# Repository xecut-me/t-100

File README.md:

# Siemens Teleprinter 100

Это [телетайп](https://ru.wikipedia.org/wiki/%D0%A2%D0%B5%D0%BB%D0%B5%D1%82%D0%B0%D0%B9%D0%BF) 1963 года, который мы купили и поставили в хакспейсе. Кстати tty в линуксе берется именно отсюда.

Суть телетайпа в том, что это как печатная машинка, но подключенная по телеграфной линии. То, что печатается на клавиатуре, уходит по проводам, а то что приходит печатается на бумаге

Maximum line length = 68 symbols

# AI печатная машинка

## Установка

```bash
cd server
pip install -r requirements.txt
curl -fsSL https://deno.land/install.sh | sh
```

## Запуск

Задать переменные окружения:
- `LLAMA_API_URL` - URL LLM API (например `https://localhost:8080/v1/chat/completions`)
- `LLAMA_API_KEY` - ключ API

Запуск через сокет (подключение к телетайпу по сети):

```bash
deno run --allow-all socket_runner.ts
```

## Как работает

- `server/llm_core.py` - основная логика общения с LLM, стриминг ответов посимвольно
- `server/socket_runner.ts` - Deno скрипт для подключения к телетайпу по TCP сокету (192.168.10.124:1337)

Телетайп притворяется машиной из 1970-х (дата минус 50 лет), отвечает только символами кода Бодо ITA2.

Команда `CLR` или `CLEAR` очищает историю диалога.

# Loopback

Подключается токовая петля и тогда то что уходит, то и приходит. TODO: картинки

### Схема

<table width="100%">
  <tr>
    <td></td>
    <td></td>
  </tr>
  <tr>
    <td></td>
    <td></td>
  </tr>
</table>

## Используемый код

Используется [код Бодо ITA2](https://ru.wikipedia.org/wiki/%D0%9A%D0%BE%D0%B4_%D0%91%D0%BE%D0%B4%D0%BE#ITA2)

# Схемотехника

[Схема в circuit.js](https://www.falstad.com/circuit/circuitjs.html?ctz=CQAgjAzCAMB00IQVhBJsBs0BMAWDWGA7NEUQJxghLTXW1ICmAtGGAFABKMI5GIzDLl79atXLTw8xsJOwBOIPLWLZUEfqp4boCkZKT8+tMOTUnyuxUjBrKam3aKjwADl0BzfSFdgjWH1xXaXYAdxAhSQkI6OxDGHYAExiDTVjXYLVExgAzAEMAVwAbABdmIsZE9lwwWghoYTNgiVpXPnAcFAA-ABUAGVwIKmgAHQBnaIxxsBZbcbgiCDQMbEgkclcyWyR5+Yjx7FnsceY4V1xV3DNyG4bN6AhdsbFpk7OLsCvsG8sgkkfnrBFstVmgNls4tMJOMuiUioMZolmABHAB2AH1KjBxhBsO5sWNlC8xkRsAgCUtYEtqTTaZpprBDqxjoDSWwyEMkN91v8nioDrBcEc3vBEBpFoZyIsMmAkEQwK4ds89qMxmARYgHsRllKIDK5QqlQtVmAObLuVKHlDVbD4UNKiiMQ6AIJgRkEhWwBXe3y+n37QmMzXB4MQYWA4iuXFIVzEOVgzZ8gO4QUhtMzZnzeB+KVxGqm4E0QZJ1XqwHQHOkpD5jloBoAuCR6Oxojx9aJtXQsa2hEOtGYpHO7Du1XuYmTabhhYPChIQxYchclZJqaE8OnWCuMmxvj1dy2KVGlWvMYbrfQHcYPcV76trP-Wfz6CL7DLzs2uG9pH9rGqlrj-k1SnIEGlWasICuRco3OFcDnXOBamgLkGk+CRqyIXwSxPDdEOQmpcDQ3AMLLacPnAyCYz1XBrRhT97W-J1klHQCmFYBsgTJUkCEVCAbgItBYKAzNTwWDDKHWGhyCWbB5VcLC1RFMg2llRdn2k2T70418MB4vjBiVT4PztRFHQHZhnTgFBmIDDM5hEkDcT4dxKC3ChqOVZ4AzDYS4E1RVNhoB5sDiXFTAbY9TxI0UEH81sEFxELVikxSgqc58FRk8h3KwWjjL7AAHAcCXxVdbJZDd-hwXMlnuUgSL2VdvLst01LQc4iP4tAY3k1gGVamMCKITq5zk+zKtvbAapIOrxhy7s6JM5FCt-cYx2K8k-0Asr71lJBcT1WwZPlIjBKZOzWE3II-C619VlbUbVWJMsLvOXwrznW7TW61ldv23xgq2E731yr9TJWtUaGKgNWLshYdNqCDLA2Z85Xcx6bNmZ7hzlPhFj8ZD1khDynpObGKG1fGyUJo0gXhh4rmfZzUZo+a8oYsznSs6ZNQJCchPOlroCwAiKwwojbCCU7w2HAKiOcJYyHE6tZnCzzSwFWWyCvCBFd2oU2JOQXhYkU1znlPBRsMkH6LB5IWR7G3EiK0tECUa2TKdrFSsxhlXsgE2NmrPwiCl1hnoQ5AKwgvGhq5WM+T0f3hC0JOIgvbR6jCcAhjUFOIOT0kEnCSBbB8Pxs7xMvRCzyBK7e7OAnr3QddoYxwFLtvTX4KAxCzzuzG8Lui8HjuAnaXRwkcEACOCKeWgSIpvBkuwAlxMQYCpQK01DDfNSEOJfl4jRlEXYe2+Xpf4gn7w15vnSEgAN3AIsQEWfhZQaCJC+EFBIas6RZA13zmnYIH9k7p2vmAkBz9P5aEgToKu4ALjCCbjXZBiCoGoOLi-euUC34JEUK9agA8iEYCvh0XQABjQIwQtBENJOIJQsht4hn1kQJQKYKyQHzrgQwbQtw91FMMLOpD4ikMLroZItQpC32kcIZQShwAADkWi4GqA8JB6c47Pw0MQ8w4ByDoiEOiaA6IJA3HREgEx8A4jolYOibA6JTDoggOoqAtRJjCFsPiUw+jbBGNwCYsxz5DESGsUhOxYAHFOMca4iQ7jID8HnrYIQ09UkqACUE8xoTTG+SFrY+xEBLFBKsUUvoABRAAIlnKeCjIgcN7uEep9Rk7pGCFYFIqAySdI0O0ihWdmndOaZ-a+c9yT1PntfCZ4zoi9ISPE7OA84jv2Ql09ejjjGmOyU43J8ArH2McbEmuOAvEDzkQ04ethy64JzogyBJyDErwsOYdgLd1D8DWksD57Qe7zI0XiYIVFp7lxnjwC4mSinbLCb5bYkSnHqPYbUQuYsKHBBRdIuQxc-DBFwasD55dIHYtfucdu98SDCEJWSz+bB75wJrkSvOpc6U1FbgPBhvAB71KoL0AYQxeZbXgvAEgKxZTkoQBcdwqtAJnXKghK83IZJbiELxWwIdiYehFNdBVGFXyDHsGqjcpB8mioaOKvEVpgas1Bj+JiOJzUEiJASBhxJKS0jddSekapGTAVIINMheohDOHQmq9Gq5hz6zssOFpOslgxnJoqBUPt1Xq0DNGwsmwnI2FcEm3yQ0iL+tjPm4NLMHaLUYuZN05hpiuC9H6Ot-ow1BhYZqJqLJc1+r2ouPiOq0YNXGCmf8zbtqRVFAQZwnwuRkg2BgFg5B5LPSNsQDAE7gqMxncwOd5Y81Bt4usLKPaS0LT7OWocI5VobX7QK4ShqyHejAkEPEFAQ19rXNeuA3xlnnjMMuvUGh50ig-Xwqdr5IBRlXDerNVzqxbgzWqq2VqbY2v5ReiYV7YZCo7bxHSCAryylDudXyt7-qgWAwReqatsKEcg2SC4pGahZl9UWrDY5cMGS7KW49ztz3QxVgx7dBaKyUA6s+zy3sfKMnErKGephgSxlXOjFN77JPViurqAN8mMNMf3EJoacH2NHvZi6Sy60MbidMBsLKgVl0EFvA9F9raTgYCBPLSaWUhBsHFDmiKvVTxOa1vtNz+ZPNhyzOZtovCcN+BWFKUac0OPfmWrasYJVJxmZuOFmgH8soXD1IJBzgIBoXg0FcNgZtl09SioVsDJWFT5qimFyzFZJIEUmrFoy1rEvrWJGtTapmCOMlNA8cLq68XEF7aJuCb6qTnAVDpwwk0-ANH-fZKis3PithWEMYWAHBt6iyiNqLQ1D1s1th6SGo4ePCQgF6T6BAroleCuuuzE3+bhy9MQD+VN3B4D4G2iKb3g6faQt9q4b5rspNG-d+wr4WCW30ydm15kuZqh5r1sT-XV1tADYWqUvD5MvplSca7vFcZIQi2JOWsxHr-aJ1SG4xAyc0Ap2QKnAHtxSVjDj2OpV4fWsYm7BDHsuMo-JPbAzzBPbJHR1FVbykiJ4DxJ2-Db2hbUdAvgMhM4E7FweTpUBpBc4ZEuQbiIRukVqBRboEo3gyFGErrbxRVBmCTU3CpyIsYrN6g3lql8YklikD2u48k2R8jFBKHoJoiDI-4JUNfSP9c25YI5RbrkyfX66Lj2y3R0eM-HPTg785Dv7lSAL7ro3ceAgO6lJoK+fd7eFxz9XcIkf6mR7lE33gld2-eG7x02o8QsCgPNNAuomcdcl-iIXiBxyS-p375oaf3BSvgNAZNXOECwUMGkBvTF7dU+D-biSg-18iGExodQZwfyoB69fqn+uTdqBFM2cEixVjfL7KiY4vaLi+6N3LucpPAA--E3VBBZVsNQUFDIBgUuBgDZQJDAF-VwYJaxKJexDgcIU-S-NvS-TwagUuDxaAtQWocvM+AIbvNuOZXQbgKAnwVockfEdeWIClABXfGg-ERPRpbwdgseauFSPA3OKQKeFTCIJQEwZtJhXfIQgifg6eIIYeKeFYH+JlWvN5KeVCGQ3xVAEISefA6QqeceGpfAgeWpaIKgpQQubvYKH+HAxRP+bfSyLOC+bvUHC-auRQfAYQNACA1JAFHgMka+DwpQI3QIhRAInw6IEwzgwIrwtJYQSZLOQI+eMZTg+hbpehXPDAuQ-BRvM+S-UvfPWvBZc3cwog-w95PwpA5-KFXZCJA5BxJA1xcfTw7pc5SgmfTw++Cg++AI8udofQjvVuJJXojvNQ01GQ6veQjuUuKeHrdga3UFdlKedlIggQT0JYQYKMc1LbCCKyS6KdRAfwuMXhChEAMYfKAAS0oRYBD0KFKEMIt0-gUNr3CC+Q6BkV0QIOHleM+NGNMKzjmTbhqH8CiOGPEGuQ2gSPBMINoKiKyO6VePZWvleK0ARJGS4AuRTk5QkU3zoHXgcJeN0XJXKMRP+N0U+UJO6VGVLjWiWNzwWQvkW2nlFykFaDgJcRfxyXCQ-3hSAA)

# Оригинальная документация

- t100fullmanual.pdf - для человеков
- t100fullmanual.txt - OCR as is, для LLM-ок

# Тематические стикеры

# Фича с отправкой своего адреса

Есть спец код который посылаешь 2 раза и машина печатает свой адрес

Адрес кодируется вот такими пинами

# Прочая информация

1.8W raspberry
4.2W raspberry + arduino

## Форматтеры

- autopep8
- clang format

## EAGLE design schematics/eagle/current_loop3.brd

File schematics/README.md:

# Схема адаптера токовой петли

## Отступления схемы от реального железа

1. Q2 установлен BD139 (может быть установлен MJE340)
2. Вместо D2 установлена пара из встречно включенных стабилитронов на 24 вольта (при установке 1n4004, не хватает быстродействия и телетайп не отпускает селекторный магнит достаточно быстро).

## Настройка

1. настроить повышающий преобразователь для питания токовой петли до ~24вольт
2. подключить преобразователь к разъёму SV1
3. замкнуть разъём токовой петли на TX (XOUT) через амперметр.
4. резистором R8 настроить рабочий ток в 40мА.
5. разомкнуть TX, замнуть RX (XIN) через амперметр
6. резистором R1 настроить рабочий ток в 40мА.
7. подключить к XOUT резистор соответствующий примерно сопротивлению катушки телетайпа.
8. контролируя ток через резистор - убавить напряжение на повышающем преобразователе токовой петли до начала снижения тока
9. слегка поднять напряжение на преобразователе.

Шаги 7-9 нужны для снижения рассеиваемой мощности на транзисторах регулятора тока.

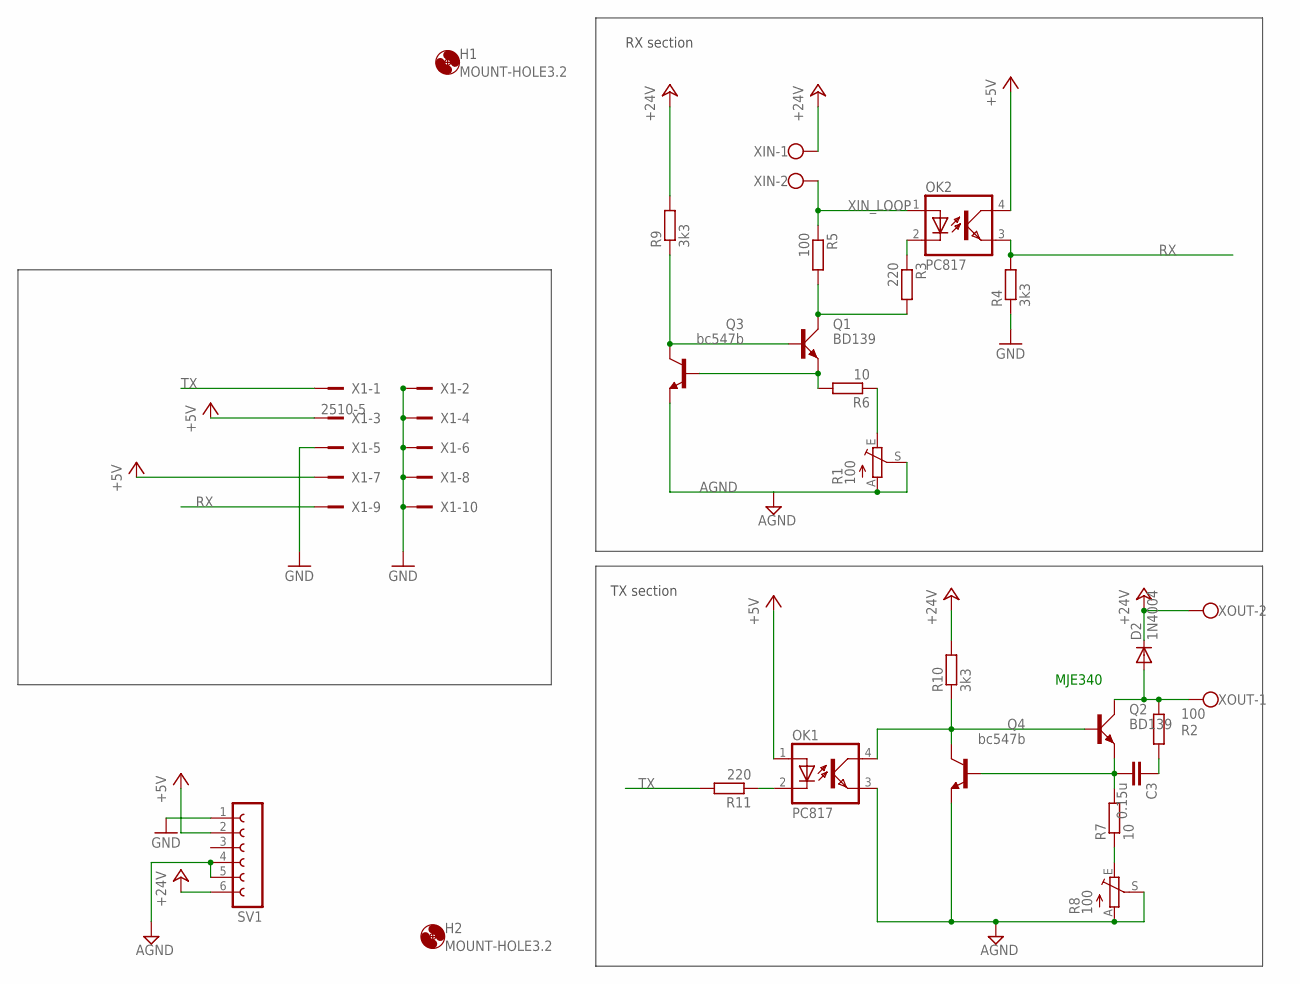
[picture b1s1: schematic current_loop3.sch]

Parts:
C3: 0.15u; C075-063X106
D2: 1N4004; DO41-10
H1, H2: MOUNT-HOLE3.2; 3,2
OK1, OK2: PC817; DIL04
Q1, Q2: BD139; TO126AV
Q3, Q4: bc547b; TO92-CBE
R1, R8: 100; CA14H
R2, R5: 100; 0204V
R3, R11: 220; 0204V
R4, R10: 3k3; 0204V
R6: 10; 0204/7
R7: 10; 0204V
R9: 3k3; 0204/7
SV1: FE06-1; FE06
X1: 2510-5; PAK100/2500-5-10
XIN: W237-102
XOUT: W237-102

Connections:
+5V: OK1.1 (A), OK2.4 (COL), SV1.2, X1.3, X1.7
+24V: D2.C, R9.2, R10.2, SV1.6, XIN.1, XOUT.2
AGND: OK1.3 (EMIT), Q3.E, Q4.E, R1.A, R1.S, R8.A, R8.S, SV1.4, SV1.5
GND: R4.1, SV1.1, X1.2, X1.4, X1.5, X1.6, X1.8, X1.10
unnamed: Q1.C, R3.2, R5.2
unnamed: R7.1, R8.E
unnamed: R1.E, R6.1
unnamed: C3.1, R2.1
unnamed: OK2.2 (C), R3.1
unnamed: OK1.2 (C), R11.1
unnamed: D2.A, Q2.C, R2.2, XOUT.1
unnamed: Q1.E, Q3.B, R6.2
unnamed: OK1.4 (COL), Q2.B, Q4.C, R10.1
unnamed: C3.2, Q2.E, Q4.B, R7.2
unnamed: Q1.B, Q3.C, R9.1
RX: OK2.3 (EMIT), R4.2, X1.9
TX: R11.2, X1.1
XIN_LOOP: OK2.1 (A), R5.1, XIN.2

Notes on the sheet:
RX section
TX section
MJE340

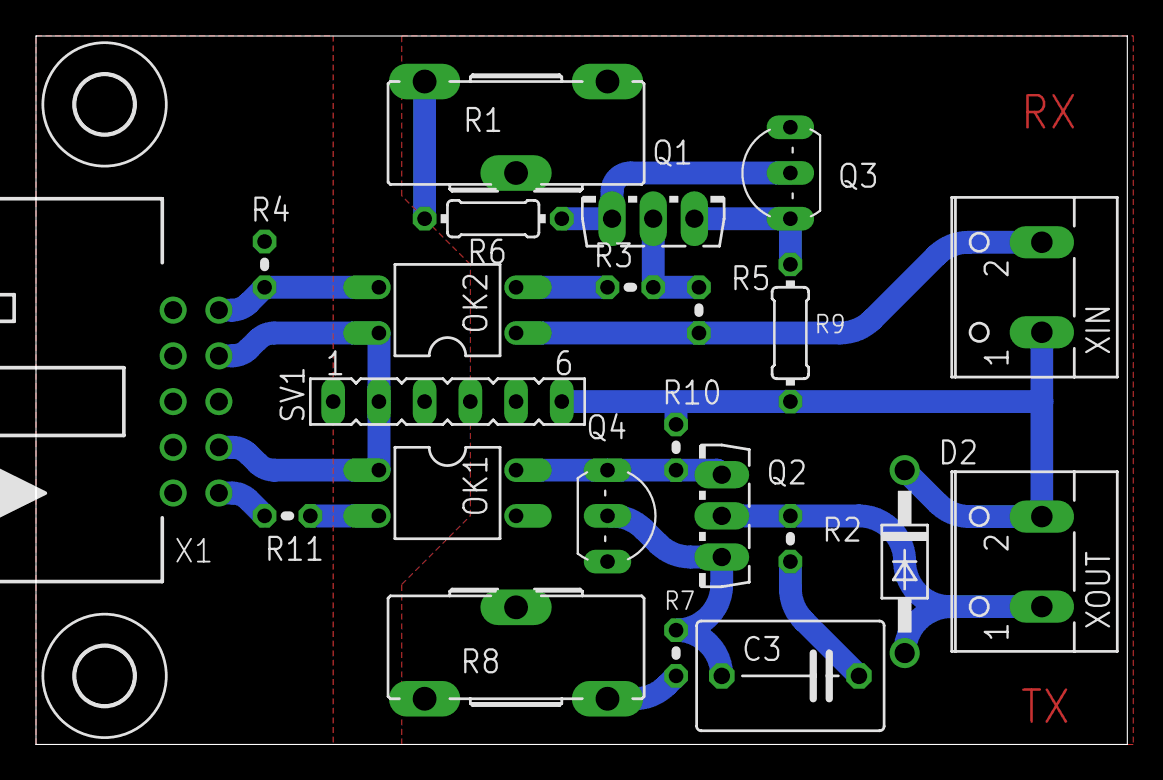
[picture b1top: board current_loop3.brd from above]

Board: 2 copper layers, 60.6 x 39.4 mm, 25 parts (0 on the bottom side), 18 nets.

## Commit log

2025-10-18 Added initial .gitignore
2025-10-18 Added build file for building outside of Arduino environment
2025-10-19 Added comments and led blinking/init
2025-10-19 Added test sequences
2025-10-19 Fixed polarities and bit order
2025-10-19 Added conversion arrays template
2025-10-19 Added initial conversion code (untested), fixed bit order.
2025-10-19 Refactoring receiver and transmitter
2025-10-19 Added conversion tables
2025-10-19 Added converted ascii->baudot and baudot->ascii mode
    Needs delays over CR/LF/motor start commands
2025-10-19 Added semi-working conversion code
2025-10-25 Fixed transmit logic
2025-10-25 Initial xon/xoff flow control added
2025-10-25 Added sending xon after reboot
2025-11-09 Added schematics and documentation folders
2025-11-09 Added photos of hardware
2025-11-09 Enabled LFS, added documentation
2025-11-09 Перенес доку на главную + добавил инфы
2025-11-09 more info
2025-11-09 applied formatting
2025-11-09 Fixed comments damaged by formatting
2025-11-10 Replace images with a table for better layout
2025-11-10 AI + T100 = LOVE
2025-11-10 docs & no deutch & longer wait
2025-11-10 lfs for 3d
2025-11-11 deutch
2025-11-14 Moved arduino code to subfolder, due to build breakage from export.c code
2025-11-14 Implemented byte counting for teletype
2025-11-14 Implemented loopback mode
2025-11-15 Fixed makefile to avoid patching arduino-mk
2025-11-15 pyserial
2025-11-15 llama key, info, python reqs
2025-11-15 ttyACM (another arduino)
2025-11-15 germal flag
2025-11-15 system prompt signalling
2025-11-20 Added timer variable
2025-11-22 Initial commit for esp32-c6 port
2025-11-23 pyserial2
2025-11-26 Gui rework
2025-11-26 Added serial1 at 50 baud
2025-11-26 Fixes to gui + cleanup
2025-11-26 Show real buffer status
2025-11-26 Refactored rx/tx section, for use without protothreads
2025-11-26 Refactoring 2
2025-11-26 Refactored special character treatment.
    Added indicator of current letters/symbols status on rx/tx
2025-11-27 Network works
2025-11-27 Cleanup. Added buffers status. Fixed bug with waiting.
2025-11-27 Added makefile
2025-11-27 Minor refactoring
2025-12-02 Added buffer and status reset on disconnect
2025-12-02 Makefile cleanup
    Serial restart
2025-12-03 Cleanup
2025-12-03 Added gitignore
2025-12-06 Updated oled handling
2025-12-06 Reduced timings to 500ms for linefeed and carriage return
2025-12-06 Added configuration to Makefile
2026-01-02 Preliminarily enabled OTA, removed telnet negotitation
2026-01-04 russian mode
2026-01-04 server init
2026-01-08 Implemented parallel build
2026-01-08 Separated serial handling into serial.cpp/serial.hpp
2026-01-08 Dependency fixes
2026-01-17 llm server
2026-01-31 Added initial version of hardware doc
2026-01-31 Added description of hardware tuning
2026-01-31 Added gerbers
2026-01-31 Added eagle files
